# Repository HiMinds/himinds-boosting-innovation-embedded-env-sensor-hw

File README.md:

# himinds-env-sensor-hw
HiMinds Open Source Wireless Environmental Sensor HW.

## Rev B (G2)
The second generation of the hardware is based on the first version of the hardware but we have made several improvements. It is a rechargeable battery-operated wireless sensor that can measure:

* Carbon dioxide (CO₂) levels
* Temperature with ±1.0°C accuracy
* Barometric pressure with 1 hPa absolute accuracy
* Humidity with ±3% accuracy
* Volatile organic compounds (VOC) gas sensor
* Tamper detection
* Sound level meter 

The project is described in our [Medium articles](https://medium.com/himinds/himinds-wireless-environmental-sensor-gen-2-part-1-requirements-37ee416b31b).

The enclosure is called CBRS01VWH and is made by [CamdenBoss](https://www.camdenboss.com/). 

## Rev A (G1)

The first version of the hardware, was based on the work done by OLIMEX. Link to their [project page](https://github.com/OLIMEX/ESP32-DevKit-LiPo)
For other credits please refer to our [Medium ariticles](https://medium.com/himinds/open-source-wireless-environmental-sensor-part-1-requirements-8598c5b5f503).

## Open Source Hardware
The hardware is certified by OSHWA’s Open Source Hardware Certification program.
It is the first certification given to a Swedish project. 
* Rev A (Version 1.0) [OSHWA certification](https://certification.oshwa.org/se000001.html)
* Rev B (Version 2.0) [OSHWA certification](https://certification.oshwa.org/se000007.html)

## License
* Hardware is released under Apache 2.0 License
* Documentation is released under CC BY-SA 3.0

## Disclaimer of Warranties and Limitation of Liability. (from CC 3.0)

### Representations, Warranties and Disclaimer

UNLESS OTHERWISE MUTUALLY AGREED TO BY THE PARTIES IN WRITING, LICENSOR OFFERS THE WORK AS-IS AND MAKES NO REPRESENTATIONS OR WARRANTIES OF ANY KIND CONCERNING THE WORK, EXPRESS, IMPLIED, STATUTORY OR OTHERWISE, INCLUDING, WITHOUT LIMITATION, WARRANTIES OF TITLE, MERCHANTIBILITY, FITNESS FOR A PARTICULAR PURPOSE, NONINFRINGEMENT, OR THE ABSENCE OF LATENT OR OTHER DEFECTS, ACCURACY, OR THE PRESENCE OF ABSENCE OF ERRORS, WHETHER OR NOT DISCOVERABLE. SOME JURISDICTIONS DO NOT ALLOW THE EXCLUSION OF IMPLIED WARRANTIES, SO SUCH EXCLUSION MAY NOT APPLY TO YOU.

### Limitation on Liability. 
EXCEPT TO THE EXTENT REQUIRED BY APPLICABLE LAW, IN NO EVENT WILL LICENSOR BE LIABLE TO YOU ON ANY LEGAL THEORY FOR ANY SPECIAL, INCIDENTAL, CONSEQUENTIAL, PUNITIVE OR EXEMPLARY DAMAGES ARISING OUT OF THIS LICENSE OR THE USE OF THE WORK, EVEN IF LICENSOR HAS BEEN ADVISED OF THE POSSIBILITY OF SUCH DAMAGES.

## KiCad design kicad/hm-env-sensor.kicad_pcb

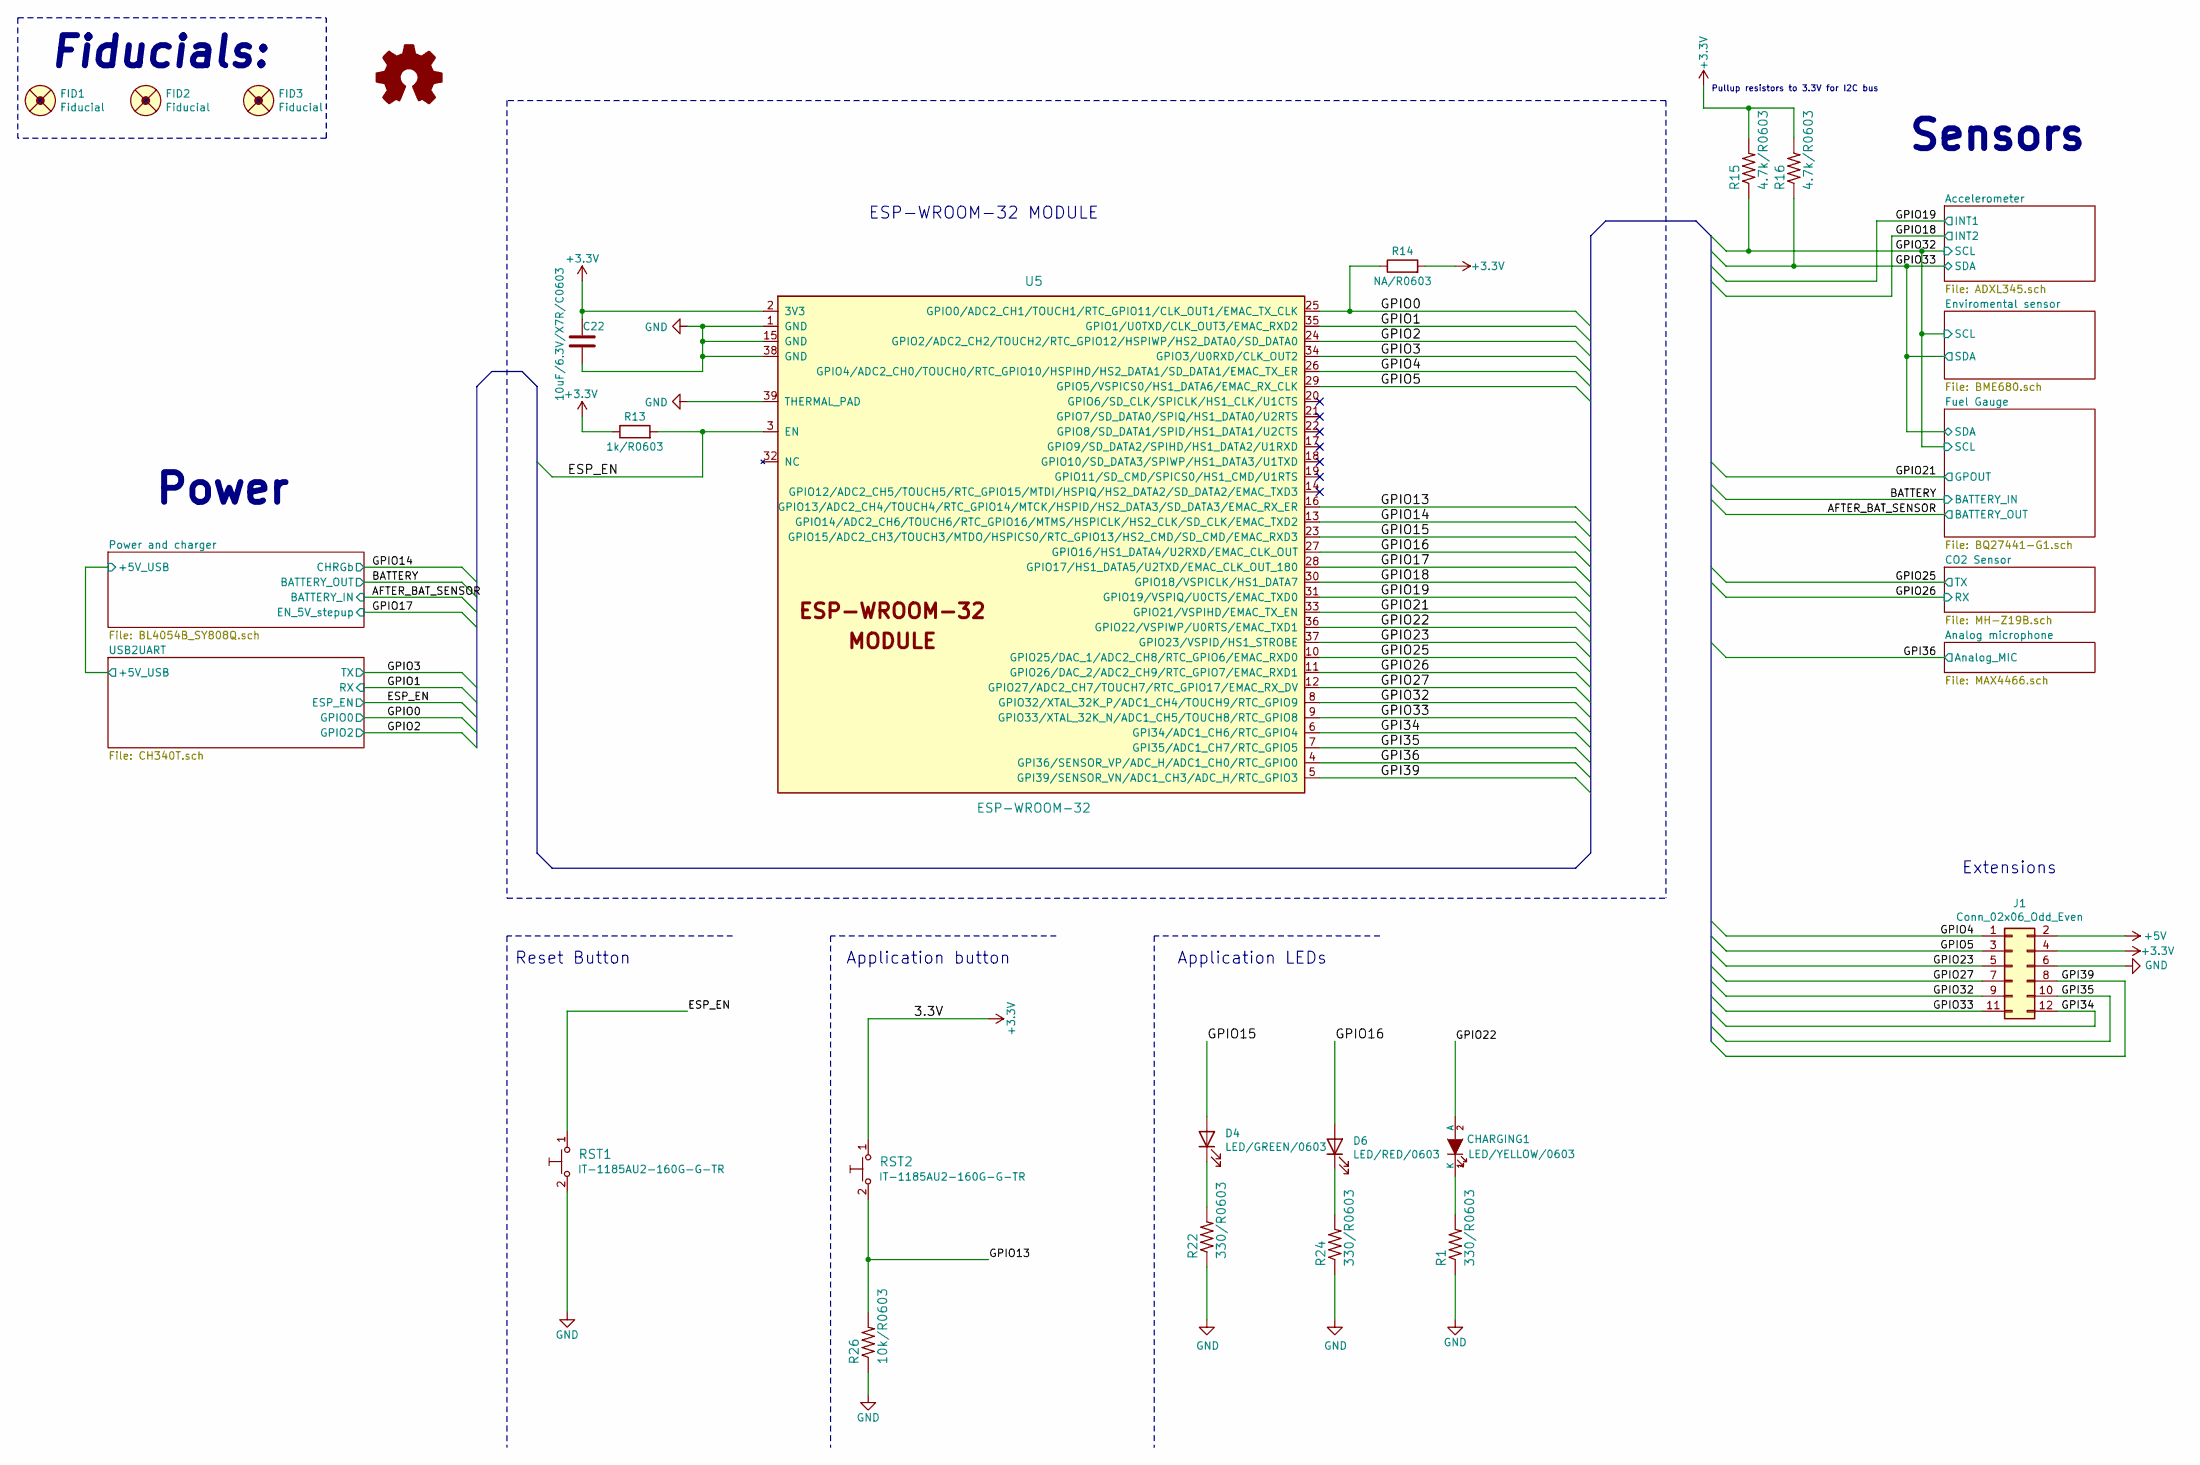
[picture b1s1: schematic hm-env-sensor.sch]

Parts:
C22: 10uF/6.3V/X7R/C0603; C_0603_5MIL_DWS
CHARGING1: LED/YELLOW/0603; LED_0603_KA
D4: LED/GREEN/0603; LED_0603_KA
D6: LED/RED/0603; LED_0603_KA
FID1, FID2, FID3: Fiducial; Fiducial1x3
J1: Conn_02x06_Odd_Even; PinHeader_2x06_P2.54mm_Vertical
R1, R22, R24: 330/R0603; R_0603_5MIL_DWS
R13: 1k/R0603; R_0603_5MIL_DWS
R14: NA/R0603; R_0603_5MIL_DWS
R15, R16: 4.7k/R0603; R_0603_5MIL_DWS
R26: 10k/R0603; R_0603_5MIL_DWS
RST1, RST2: IT-1185AU2-160G-G-TR; IT1185AU2_V2
U5: ESP-WROOM-32; ESP-WROOM-32_MODULE

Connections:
+3V3: C22.1, J1.4, R13.1, R14.2, R15.2, R16.2, RST2.1, U5.2 (3V3); also elsewhere on the board
+5V: J1.2; also elsewhere on the board
/ESP_EN: R13.2, RST1.1, U5.3 (EN); also elsewhere on the board
/GPI34: J1.12, U5.6 (GPI34/ADC1_CH6/RTC_GPIO4)
/GPI35: J1.10, U5.7 (GPI35/ADC1_CH7/RTC_GPIO5)
/GPI36: U5.4 (GPI36/SENSOR_VP/ADC_H/ADC1_CH0/RTC_GPIO0); also elsewhere on the board
/GPI39: J1.8, U5.5 (GPI39/SENSOR_VN/ADC1_CH3/ADC_H/RTC_GPIO3)
/GPIO0: R14.1, U5.25 (GPIO0/ADC2_CH1/TOUCH1/RTC_GPIO11/CLK_OU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); also elsewhere on the board
/GPIO1: U5.35 (GPIO1/U0TXD/CLK_OUT3/EMAC_RXD2); also elsewhere on the board
/GPIO2: U5.24 (GPIO2/ADC2_CH2/TOUCH2/RTC_GPIO12/HSPIWP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); also elsewhere on the board
/GPIO3: U5.34 (GPIO3/U0RXD/CLK_OUT2); also elsewhere on the board
/GPIO4: J1.1, U5.26 (GPIO4/ADC2_CH0/TOUCH0/RTC_GPIO10/HSPIHD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)
/GPIO5: J1.3, U5.29 (GPIO5/VSPICS0/HS1_DATA6/EMAC_RX_CLK)
/GPIO13: R26.2, RST2.2, U5.16 (GPIO13/ADC2_CH4/TOUCH4/RTC_GPIO14/MTCK/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)
/GPIO14: U5.13 (GPIO14/ADC2_CH6/TOUCH6/RTC_GPIO16/MTMS/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); also elsewhere on the board
/GPIO15: D4.2 (A), U5.23 (GPIO15/ADC2_CH3/TOUCH3/MTDO/HSPICS0/RTC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)
/GPIO16: D6.2 (A), U5.27 (GPIO16/HS1_DATA4/U2RXD/EMAC_CLK_OUT)
/GPIO17: U5.28 (GPIO17/HS1_DATA5/U2TXD/EMAC_CLK_OUT_180); also elsewhere on the board
/GPIO18: U5.30 (GPIO18/VSPICLK/HS1_DATA7); also elsewhere on the board
/GPIO19: U5.31 (GPIO19/VSPIQ/U0CTS/EMAC_TXD0); also elsewhere on the board
/GPIO21: U5.33 (GPIO21/VSPIHD/EMAC_TX_EN); also elsewhere on the board
/GPIO22: CHARGING1.2 (A), U5.36 (GPIO22/VSPIWP/U0RTS/EMAC_TXD1)
/GPIO23: J1.5, U5.37 (GPIO23/VSPID/HS1_STROBE)
/GPIO25: U5.10 (GPIO25/DAC_1/ADC2_CH8/RTC_GPIO6/EMAC_RX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); also elsewhere on the board
/GPIO26: U5.11 (GPIO26/DAC_2/ADC2_CH9/RTC_GPIO7/EMAC_RX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); also elsewhere on the board
/GPIO27: J1.7, U5.12 (GPIO27/ADC2_CH7/TOUCH7/RTC_GPIO17/EMAC_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)
/GPIO32: J1.9, R15.1, U5.8 (GPIO32/XTAL_32K_P/ADC1_CH4/TOUCH9/RTC_G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); also elsewhere on the board
/GPIO33: J1.11, R16.1, U5.9 (GPIO33/XTAL_32K_N/ADC1_CH5/TOUCH8/RTC_G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); also elsewhere on the board
GND: C22.2, J1.6, R1.1, R22.1, R24.1, R26.1, RST1.2, U5.1 (GND), U5.15 (GND), U5.38 (GND), U5.39 (THERMAL_PAD); also elsewhere on the board
unnamed: CHARGING1.1 (K), R1.2
unnamed: D4.1 (K), R22.2
unnamed: D6.1 (K), R24.2

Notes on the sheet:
Fiducials:
ESP-WROOM-32 MODULE
Application button
Application LEDs
Reset Button
Pullup resistors to 3.3V for I2C bus
Extensions
Sensors
Power

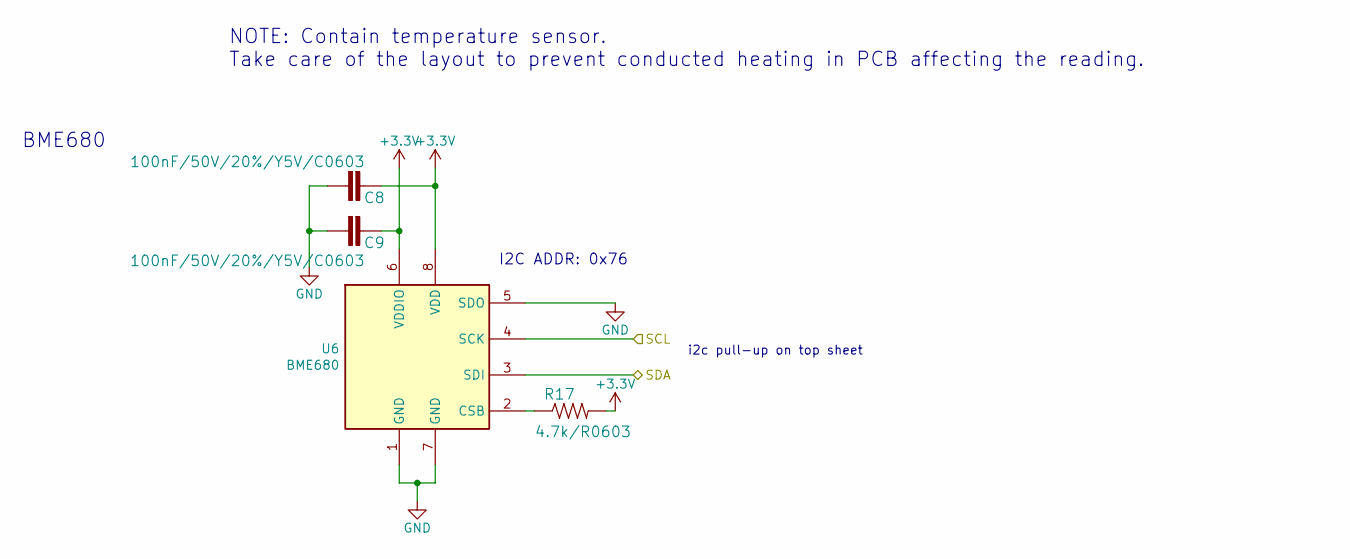
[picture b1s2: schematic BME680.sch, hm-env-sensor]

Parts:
C8, C9: 100nF/50V/20%/Y5V/C0603; C_0603_5MIL_DWS
R17: 4.7k/R0603; R_0603_5MIL_DWS
U6: BME680; Bosch_LGA-8_3x3mm_P0.8mm_ClockwisePinNumbering

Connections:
+3V3: C8.1, C9.1, R17.2, U6.6 (VDDIO), U6.8 (VDD); also elsewhere on the board
/GPIO32: U6.4 (SCK); also elsewhere on the board
/GPIO33: U6.3 (SDI); also elsewhere on the board
GND: C8.2, C9.2, U6.1 (GND), U6.5 (SDO), U6.7 (GND); also elsewhere on the board
unnamed: R17.1, U6.2 (CSB)

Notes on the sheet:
I2C ADDR: 0x76
BME680
i2c pull-up on top sheet
NOTE: Contain temperature sensor. Take care of the layout to prevent conducted heating in PCB affecting the reading.

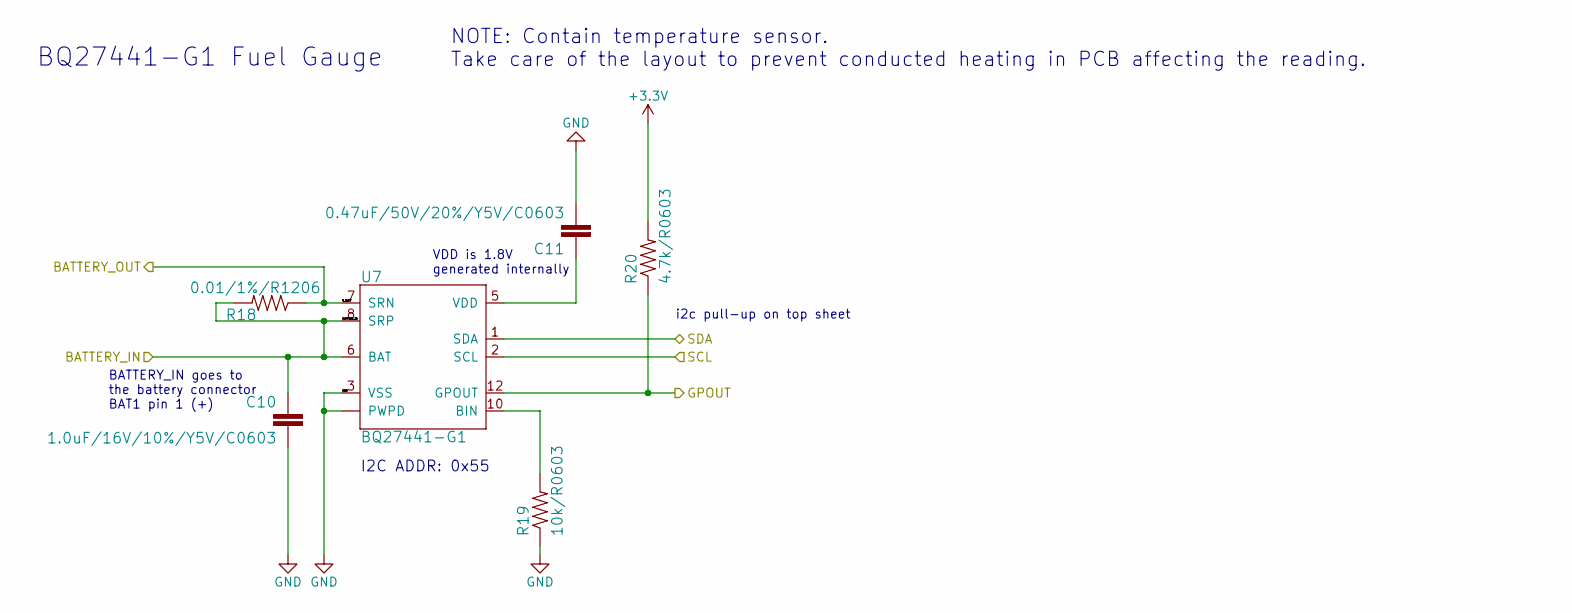
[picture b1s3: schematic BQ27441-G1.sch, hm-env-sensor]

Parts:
C10: 1.0uF/16V/10%/Y5V/C0603; C_0603_5MIL_DWS
C11: 0.47uF/50V/20%/Y5V/C0603; C_0603_5MIL_DWS
R18: 0.01/1%/R1206; R_1206_5MIL_DWS
R19: 10k/R0603; R_0603_5MIL_DWS
R20: 4.7k/R0603; R_0603_5MIL_DWS
U7: BQ27441-G1; PDSO-N12

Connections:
+3V3: R20.2; also elsewhere on the board
/AFTER_BAT_SENSOR: R18.1, U7.7 (SRN); also elsewhere on the board
/BATTERY: C10.1, R18.2, U7.6 (BAT), U7.8 (SRP); also elsewhere on the board
/GPIO21: R20.1, U7.12 (GPOUT); also elsewhere on the board
/GPIO32: U7.2 (SCL); also elsewhere on the board
/GPIO33: U7.1 (SDA); also elsewhere on the board
GND: C10.2, C11.2, R19.1, U7.3 (VSS), U7.EP (PWPD), U7.EP1 (PWPD), U7.EP2 (PWPD), U7.EP3 (PWPD), U7.EP4 (PWPD); also elsewhere on the board
unnamed: C11.1, U7.5 (VDD)
unnamed: R19.2, U7.10 (BIN)

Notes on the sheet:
I2C ADDR: 0x55
VDD is 1.8V generated internally
BQ27441-G1 Fuel Gauge
BATTERY_IN goes to the battery connector BAT1 pin 1 (+)
i2c pull-up on top sheet
NOTE: Contain temperature sensor. Take care of the layout to prevent conducted heating in PCB affecting the reading.

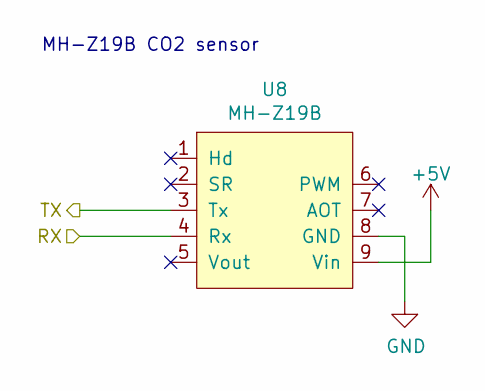
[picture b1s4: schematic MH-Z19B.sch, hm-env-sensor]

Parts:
U8: MH-Z19B

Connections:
+5V: U8.9 (Vin); also elsewhere on the board
/GPIO25: U8.3 (Tx); also elsewhere on the board
/GPIO26: U8.4 (Rx); also elsewhere on the board
GND: U8.8 (GND); also elsewhere on the board

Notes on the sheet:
MH-Z19B CO2 sensor

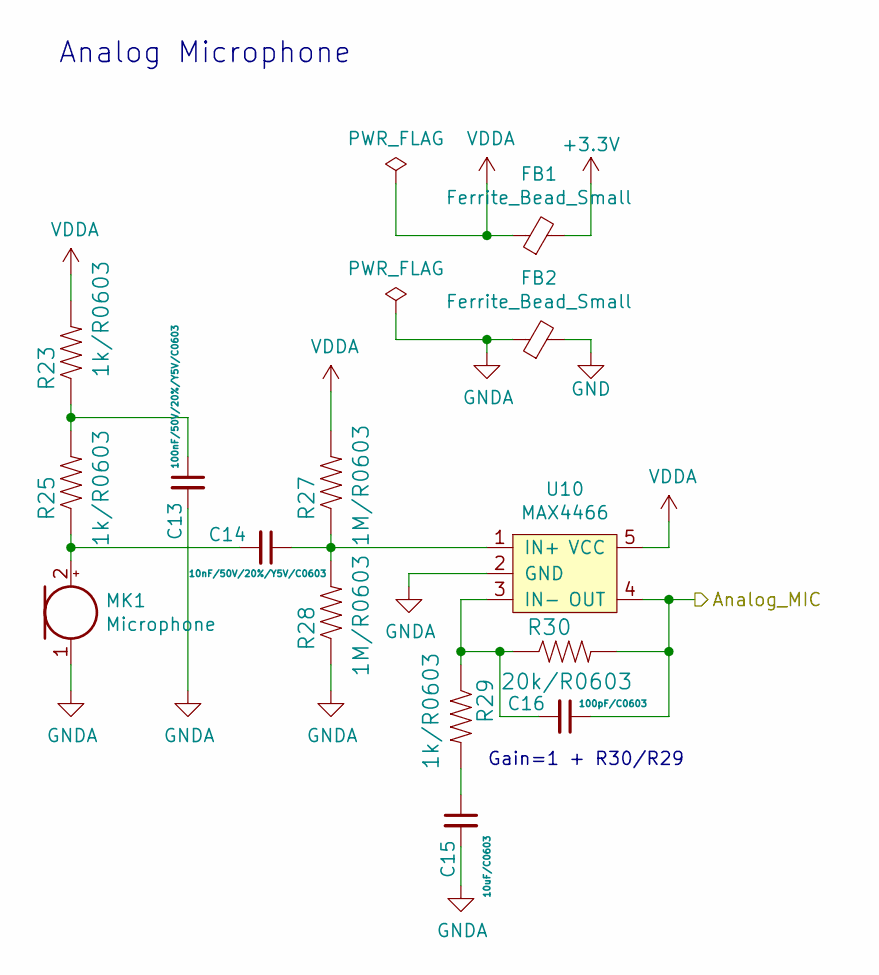
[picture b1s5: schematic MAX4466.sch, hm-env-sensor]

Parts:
C13: 100nF/50V/20%/Y5V/C0603; C_0603_5MIL_DWS
C14: 10nF/50V/20%/Y5V/C0603; C_0603_5MIL_DWS
C15: 10uF/C0603; C_0603_5MIL_DWS
C16: 100pF/C0603; C_0603_5MIL_DWS
FB1, FB2: Ferrite_Bead_Small; L_0603_5MIL_DWS
MK1: Microphone; MIC_CMA-4544PF-W
R23, R25, R29: 1k/R0603; R_0603_5MIL_DWS
R27, R28: 1M/R0603; R_0603_5MIL_DWS
R30: 20k/R0603; R_0603_5MIL_DWS
U10: MAX4466; SOT-353_SC-70-5

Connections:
+3V3: FB1.2; also elsewhere on the board
/GPI36: C16.1, R30.2, U10.4 (OUT); also elsewhere on the board
GND: FB2.2; also elsewhere on the board
GNDA: C13.2, C15.2, FB2.1, MK1.1 (-), R28.1, U10.2 (GND)
unnamed: C13.1, R23.1, R25.2
unnamed: C14.1, R27.1, R28.2, U10.1 (IN+)
unnamed: C14.2, MK1.2 (+), R25.1
unnamed: C15.1, R29.2
unnamed: C16.2, R29.1, R30.1, U10.3 (IN-)
VDDA: FB1.1, R23.2, R27.2, U10.5 (VCC)

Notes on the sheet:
Gain=1 + R30/R29
Analog Microphone

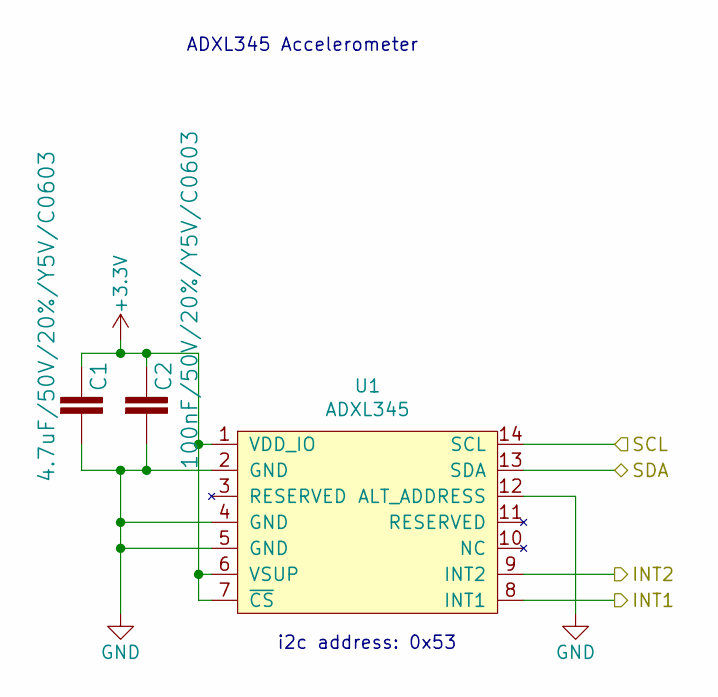
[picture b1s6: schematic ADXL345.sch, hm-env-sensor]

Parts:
C1: 4.7uF/50V/20%/Y5V/C0603; C_0603_5MIL_DWS
C2: 100nF/50V/20%/Y5V/C0603; C_0603_5MIL_DWS
U1: ADXL345; LGA-14_3x5mm_P0.8mm_LayoutBorder1x6y

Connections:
+3V3: C1.1, C2.1, U1.1 (VDD_IO), U1.6 (VSUP), U1.7 (~CS); also elsewhere on the board
/GPIO18: U1.9 (INT2); also elsewhere on the board
/GPIO19: U1.8 (INT1); also elsewhere on the board
/GPIO32: U1.14 (SCL); also elsewhere on the board
/GPIO33: U1.13 (SDA); also elsewhere on the board
GND: C1.2, C2.2, U1.2 (GND), U1.4 (GND), U1.5 (GND), U1.12 (ALT_ADDRESS); also elsewhere on the board

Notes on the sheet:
i2c address: 0x53
ADXL345 Accelerometer

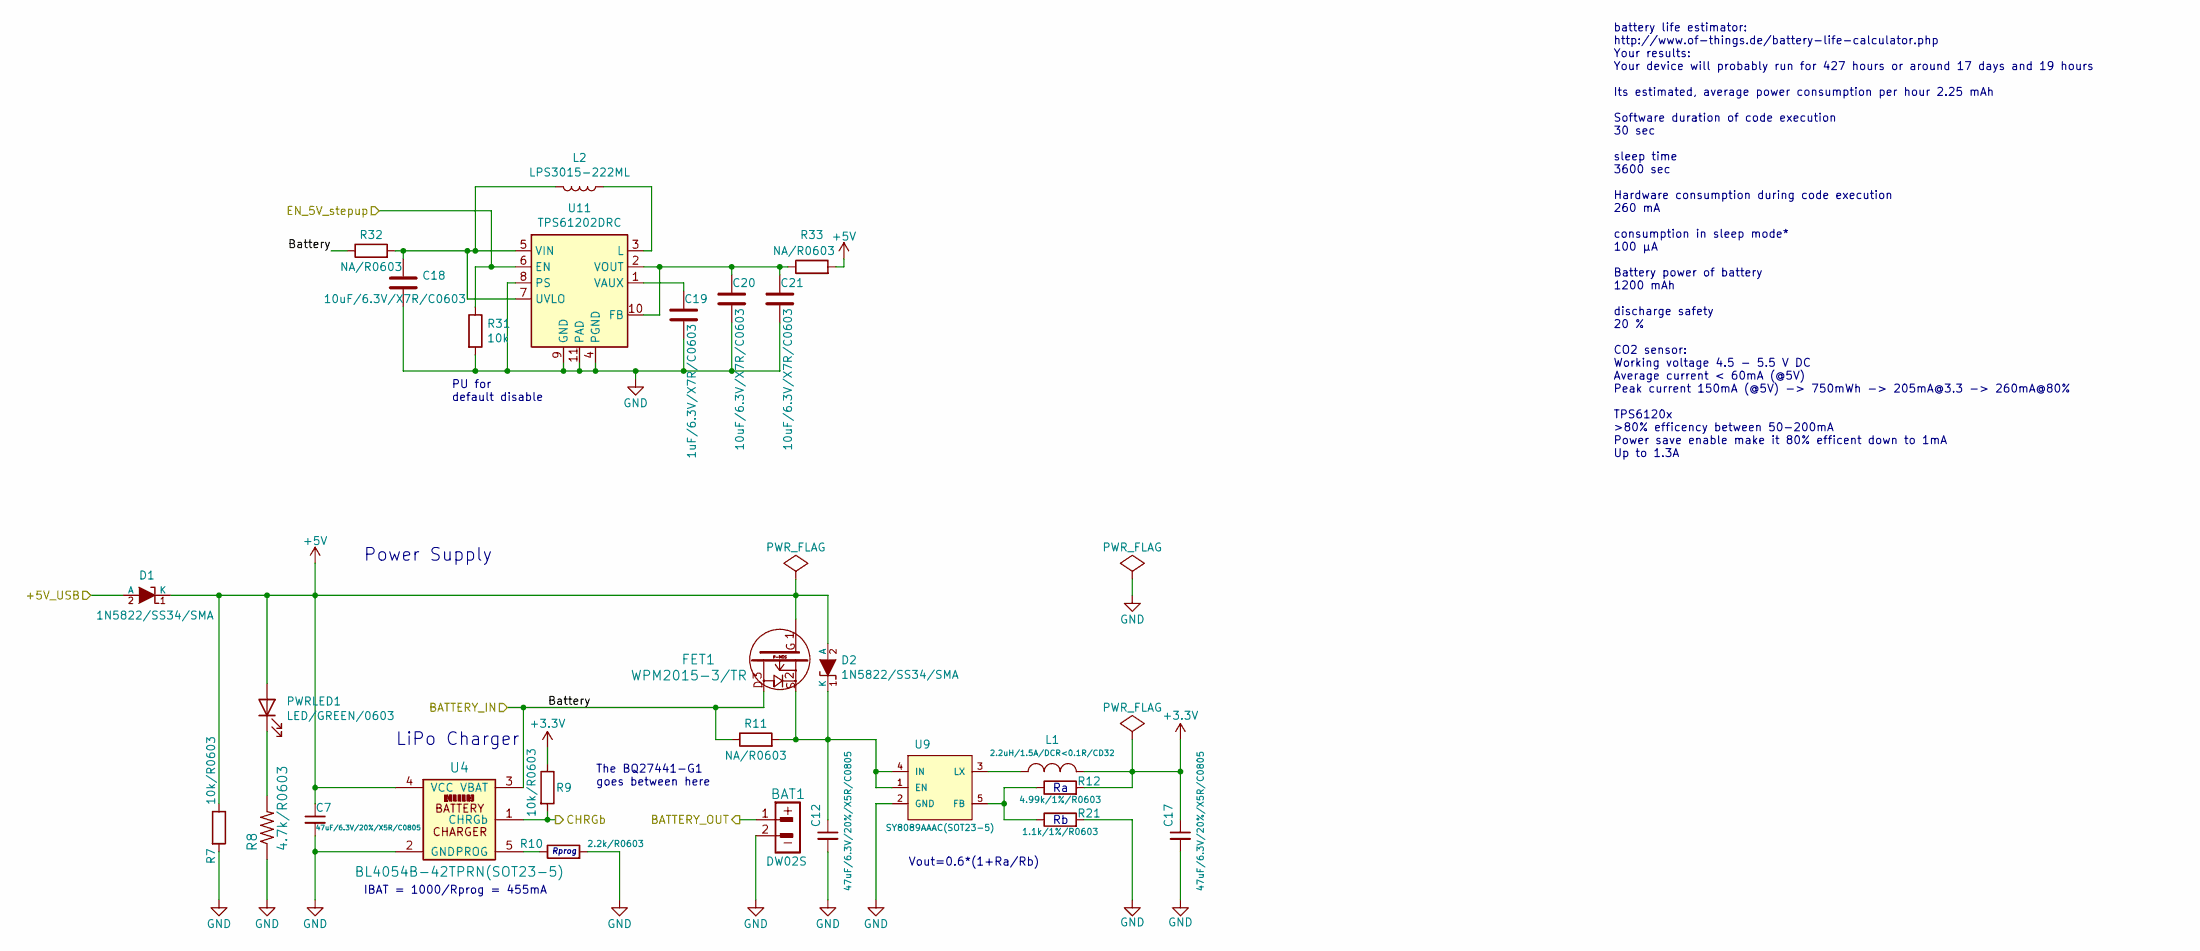
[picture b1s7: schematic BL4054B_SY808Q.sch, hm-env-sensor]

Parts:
BAT1: DW02S; LIPO_BAT-CON2DW02R
C7, C12, C17: 47uF/6.3V/20%/X5R/C0805; C_0805_5MIL_DWS
C18, C20, C21: 10uF/6.3V/X7R/C0603; C_0603_5MIL_DWS
C19: 1uF/6.3V/X7R/C0603; C_0603_5MIL_DWS
D1, D2: 1N5822/SS34/SMA; SMA-KA
FET1: WPM2015-3/TR; SOT23
L1: 2.2uH/1.5A/DCR<0.1R/CD32; CD32
L2: LPS3015-222ML; L_Wuerth_MAPI-3015
PWRLED1: LED/GREEN/0603; LED_0603_KA
R7, R9: 10k/R0603; R_0603_5MIL_DWS
R8: 4.7k/R0603; R_0603_5MIL_DWS
R10: 2.2k/R0603; R_0603_5MIL_DWS
R11, R32, R33: NA/R0603; R_0603_5MIL_DWS
R12: 4.99k/1%/R0603; R_0603_5MIL_DWS
R21: 1.1k/1%/R0603; R_0603_5MIL_DWS
R31: 10k; R_0603_5MIL_DWS
U4: BL4054B-42TPRN(SOT23-5); SOT-23-5
U9: SY8089AAAC(SOT23-5); SOT-23-5
U11: TPS61202DRC; Texas_S-PVSON-N10_ThermalVias

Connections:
+3V3: C17.1, L1.2, R9.1, R12.2; also elsewhere on the board
+5V: C7.1, D1.1 (K), D2.2 (A), FET1.1, PWRLED1.2 (A), R7.1, R33.2, U4.4 (VCC); also elsewhere on the board
/AFTER_BAT_SENSOR: FET1.3, R11.1, R32.1, U4.3 (VBAT); also elsewhere on the board
/BATTERY: BAT1.1; also elsewhere on the board
/GPIO14: R9.2, U4.1 (CHRGb); also elsewhere on the board
/GPIO17: R31.1, U11.6 (EN); also elsewhere on the board
/Power and charger/+5V_USB: D1.2 (A); also elsewhere on the board
GND: BAT1.2, C7.2, C12.2, C17.2, C18.2, C19.2, C20.2, C21.2, R7.2, R8.1, R10.2, R21.2, R31.2, U4.2 (GND), U9.2 (GND), U11.4 (PGND), U11.8 (PS), U11.9 (GND), U11.11 (PAD); also elsewhere on the board
unnamed: C12.1, D2.1 (K), FET1.2, R11.2, U9.1 (EN), U9.4 (IN)
unnamed: C18.1, L2.2, R32.2, U11.5 (VIN), U11.7 (UVLO)
unnamed: C19.1, U11.1 (VAUX)
unnamed: C20.1, C21.1, R33.1, U11.2 (VOUT), U11.10 (FB)
unnamed: L1.1, U9.3 (LX)
unnamed: L2.1, U11.3 (L)
unnamed: PWRLED1.1 (K), R8.2
unnamed: R10.1, U4.5 (PROG)
unnamed: R12.1, R21.1, U9.5 (FB)

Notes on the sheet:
Vout=0.6*(1+Ra/Rb)
Power Supply
LiPo Charger
IBAT = 1000/Rprog = 455mA
Rprog
The BQ27441-G1 goes between here
battery life estimator: http://www.of-things.de/battery-life-calculator.php Your results: Your device will probably run for 427 hours or around 17 days and 19 hours Its estimated, average power consumption per hour 2.25 mAh Software duration of code execution 30 sec sleep time 3600 sec Hardware con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
PU for default disable

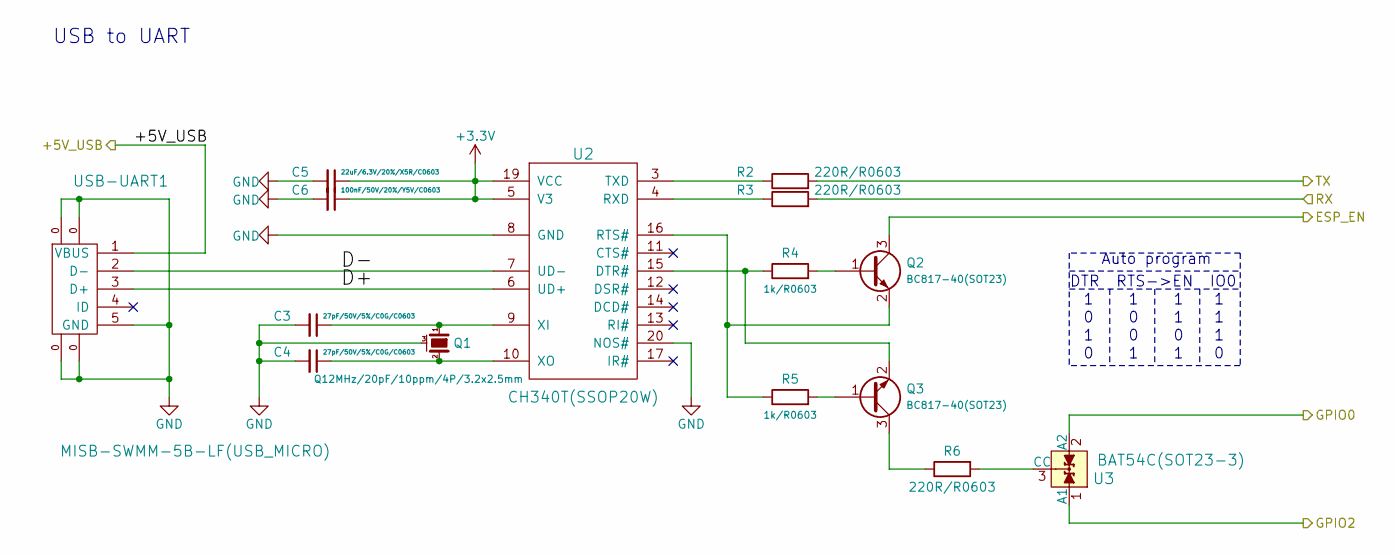
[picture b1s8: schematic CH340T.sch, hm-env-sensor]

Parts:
C3, C4: 27pF/50V/5%/C0G/C0603; C_0603_5MIL_DWS
C5: 22uF/6.3V/20%/X5R/C0603; C_0603_5MIL_DWS
C6: 100nF/50V/20%/Y5V/C0603; C_0603_5MIL_DWS
Q1: Q12MHz/20pF/10ppm/4P/3.2x2.5mm; TSX-3.2x2.5mm_GND(3)
Q2, Q3: BC817-40(SOT23); SOT23
R2, R3, R6: 220R/R0603; R_0603_5MIL_DWS
R4, R5: 1k/R0603; R_0603_5MIL_DWS
U2: CH340T(SSOP20W); SSOP-20W
U3: BAT54C(SOT23-3); SOT23-3
USB-UART1: MISB-SWMM-5B-LF(USB_MICRO); USB_Micro_B_Male_UJ2-MIBH-4-SMT-TR

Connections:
+3V3: C5.1, C6.1, U2.5 (V3), U2.19 (VCC); also elsewhere on the board
/ESP_EN: Q2.3 (C); also elsewhere on the board
/GPIO0: U3.2 (A2); also elsewhere on the board
/GPIO1: R3.2; also elsewhere on the board
/GPIO2: U3.1 (A1); also elsewhere on the board
/GPIO3: R2.2; also elsewhere on the board
/Power and charger/+5V_USB: USB-UART1.1 (VBUS); also elsewhere on the board
/USB2UART/D+: U2.6 (UD+), USB-UART1.3 (D+)
/USB2UART/D-: U2.7 (UD-), USB-UART1.2 (D-)
GND: C3.2, C4.2, C5.2, C6.2, Q1.3 (case), U2.8 (GND), U2.20 (NOS#), USB-UART1.0, USB-UART1.5 (GND); also elsewhere on the board
unnamed: C3.1, Q1.1, U2.9 (XI)
unnamed: C4.1, Q1.2, U2.10 (XO)
unnamed: Q2.1 (B), R4.2
unnamed: Q2.2 (E), R5.1, U2.16 (RTS#)
unnamed: Q3.1 (B), R5.2
unnamed: Q3.2 (E), R4.1, U2.15 (DTR#)
unnamed: Q3.3 (C), R6.1
unnamed: R2.1, U2.3 (TXD)
unnamed: R3.1, U2.4 (RXD)
unnamed: R6.2, U3.3 (CC)

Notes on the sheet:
Auto program
DTR RTS->EN IO0
USB to UART

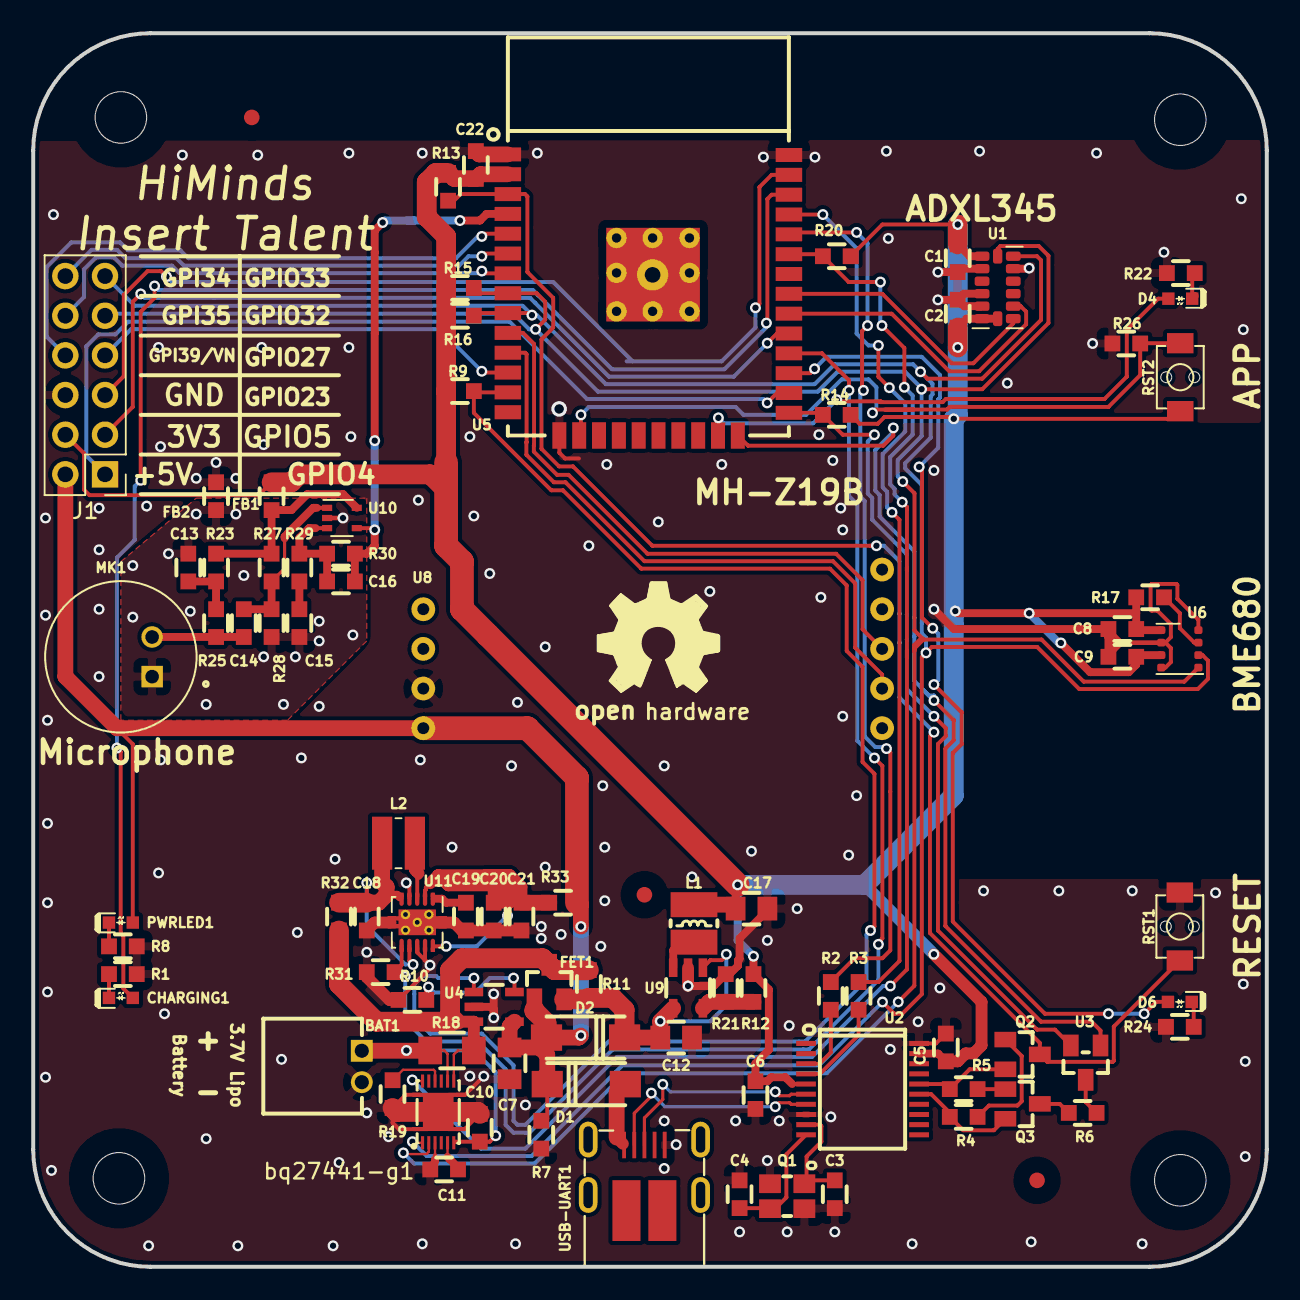
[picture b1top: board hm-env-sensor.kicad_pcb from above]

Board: 2 copper layers, 79.0 x 79.0 mm, 93 parts (0 on the bottom side), 66 nets.

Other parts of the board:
MountingHole*: Mounting_hole_3.3mm
MountingHole*#2, MountingHole*#3, MountingHole*#4: Mounting_hole_3.3mm

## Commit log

2019-11-23 added KiCad EDA files
    added KiCad EDA files
2019-11-23 Added that the certification is pending.
2020-01-20 Added folder with production files
2020-11-03 Rev B updates
2020-11-05 added BOM
2020-11-06 Update BOM
2020-11-06 Rename
